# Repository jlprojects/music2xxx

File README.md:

# music2xxx
## Hybrid Music 2000 Clone Midi I/O PCB

This is a hardware clone of the Hybrid Music 2000 Midi add-on for the Acorn BBC Microcomputer model B and Master 128 designed for use with the Hybrid Music 5000 system. It is designed to stack on the Music5xxx clone PCB, and uses the 5V supply from the main board. If used independently of the Music5xxx, you will need to provide a 5V supply - this can come from the BBC Micro's auxiliary power connector.

The Music 2000 Midi interface combined with the AMPLE programming language and the Hybrid Studio 5000 Studio software provides versatile control of external Midi devices. The Music 2000 has 3 Midi output sockets.

Despite having an on-board Midi input port, AMPLE and the Hybrid System cannot use it directly. It is assumed that the Hybrid system is used as a controller and sequencer. However, it is possible to address the interface from user programs.

## The clone

It is designed in Kicad, based upon Colin Fraser's reverse-engineered schematic. http://www.colinfraser.com/m5000/m2000sch.pdf This version uses a different opto-isolator on the Midi input, and implements activity LEDs for the Midi outputs. 

Currently all the 74xx series logic ICs are available new. The 6850 UART ICs are no longer manufactured, but are commonly available second-hand or new-old-stock. 

4/9/19 For standalone use, an optional LM7805 regulator is added to allow powering the board from 9V-12V, as well as an LED to show input activity. A few prototype PCBs have been ordered.

## Using outside the Hybrid system

It's possible to use the m2000 Midi interface in BASIC or machine code - the 6850 Uarts can be read to or written to at addresses: 

* FC08/9 ACIA 1 (MIDI OUT 1)
* FC0A/B ACIA 2 (MIDI OUT 2)
* FC0C/D ACIA 3 (MIDI OUT 3, MIDI IN)

Info from: http://mdfs.net/Info/Comp/BBC/MIDI/m2000

## Resources

* Colin Fraser's Music5000 Resources: http://www.colinfraser.com/m5000/m5000.htm

* The Music2000 Interface User Guide covers all aspects of controlling Midi instruments with AMPLE and Studio 5000. It's available on the retro-kit archive page describing the Hybrid Music 2000: https://www.retro-kit.co.uk/page.cfm/content/Hybrid-Music-2000-Interface/

* A comprehensive archive about the Hybrid Music System: https://www.retro-kit.co.uk/page.cfm/content/Hybrid-Music-5000-Synthesiser/

* Here's the Stardot thread about this project: https://stardot.org.uk/forums/viewtopic.php?f=3&t=16895

* The Stardot 8bit hardware forum often has posts about the Hybrid Music system: https://stardot.org.uk/forums/viewforum.php?f=3

* Information about Midi on the BBC Microcomputer: http://mdfs.net/Info/Comp/BBC/MIDI/

## Licence

Unless otherwise marked, work in this repository is licenced under [Creative Commons Attribution-ShareAlike 4.0 International License](http://creativecommons.org/licenses/by-sa/4.0/)

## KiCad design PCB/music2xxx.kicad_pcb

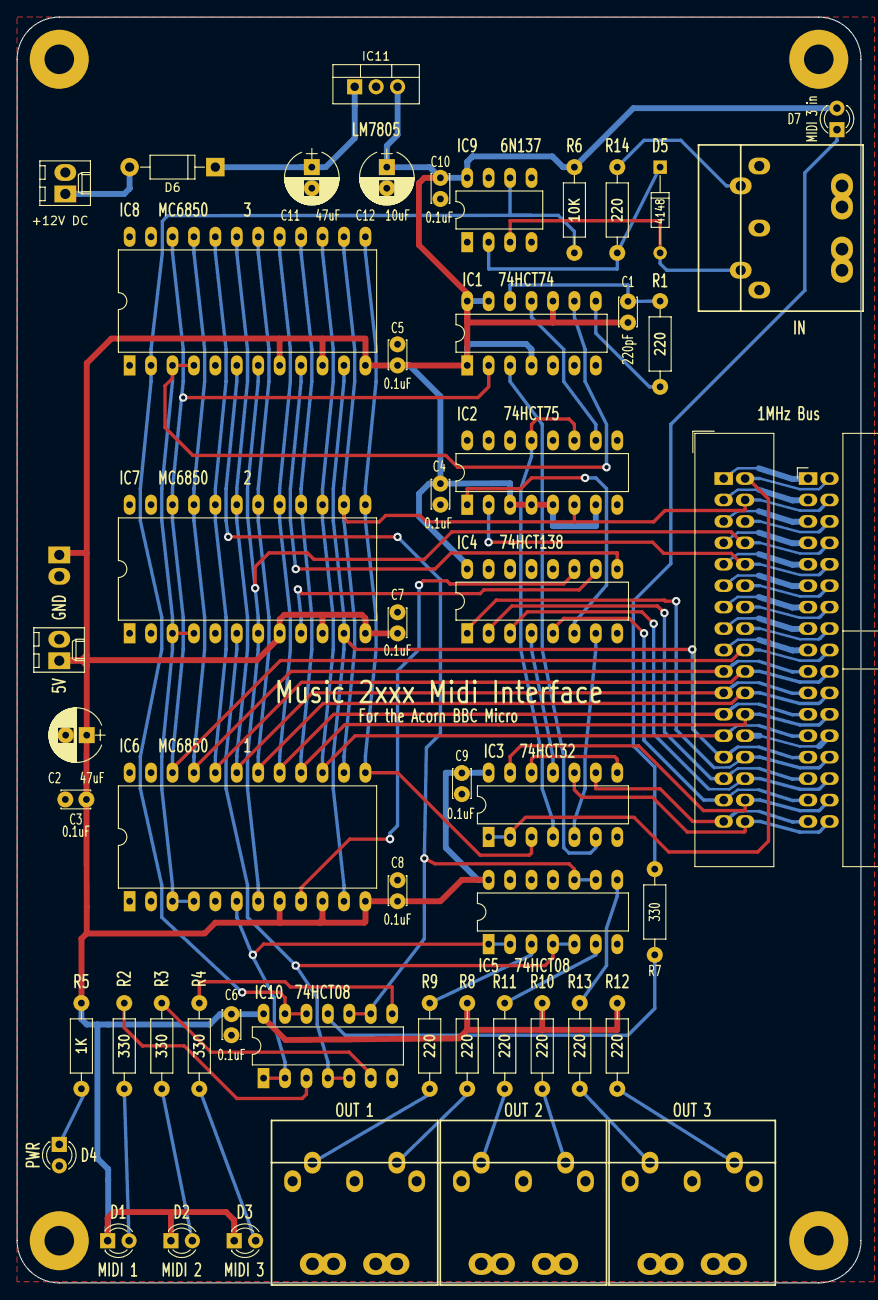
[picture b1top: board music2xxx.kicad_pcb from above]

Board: 2 copper layers, 100.0 x 150.0 mm, 57 parts (1 on the bottom side), 67 nets.

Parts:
C1: 220pF; C_Disc_D3.4mm_W2.1mm_P2.50mm
C2, C11: 47uF; CP_Radial_D6.3mm_P2.50mm
C3, C4, C5, C6, C7, C8, C9, C10: 0.1uF; C_Disc_D3.4mm_W2.1mm_P2.50mm
C12: 10uF; CP_Radial_D6.3mm_P2.50mm
D1: MIDI 1; LED_D3.0mm
D2: MIDI 2; LED_D3.0mm
D3: MIDI 3; LED_D3.0mm
D4: PWR; LED_D3.0mm
D5: 4148; D_DO-35_SOD27_P10.16mm_Horizontal
D6: 1N4001; D_DO-41_SOD81_P10.16mm_Horizontal
D7: MIDI 3 in; LED_D3.0mm
H1, H2, H3, H4: 3.5mm; MountingHole_3.5mm_Pad
IC1: 74HCT74; DIP-14_W7.62mm_LongPads
IC2: 74HCT75; DIP-16_W7.62mm_LongPads
IC3: 74HCT32; DIP-14_W7.62mm_LongPads
IC4: 74HCT138; DIP-16_W7.62mm_LongPads
IC5, IC10: 74HCT08; DIP-14_W7.62mm_LongPads
IC6, IC7, IC8: MC6850; DIP-24_W15.24mm_LongPads
IC9: 6N137; DIP-8_W7.62mm_LongPads
IC11: LM7805_TO220; TO-220-3_Vertical
J1: 1MHzBus1; IDC-Header_2x17_Pitch2.54mm_Angled
J2: 1MHzBus2; IDC-Header_2x17_Pitch2.54mm_Straight
J3, J4: +5V; Molex_KK-6410-02_02x2.54mm_Straight
J5: OUT 1; din_5_pcb_mount
J6: OUT 2; din_5_pcb_mount
J7: OUT 3; din_5_pcb_mount
J8: IN; din_5_pcb_mount
J9: +12V DC; Molex_KK-6410-02_02x2.54mm_Straight
R1, R8, R9, R10, R11, R12, R13, R14: 220; R_Axial_DIN0207_L6.3mm_D2.5mm_P10.16mm_Horizontal
R2, R3, R4, R7: 330; R_Axial_DIN0207_L6.3mm_D2.5mm_P10.16mm_Horizontal
R5: 1K; R_Axial_DIN0207_L6.3mm_D2.5mm_P10.16mm_Horizontal
R6: 10K; R_Axial_DIN0207_L6.3mm_D2.5mm_P10.16mm_Horizontal

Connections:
+5V: C1.1, C2.1, C3.1, C4.1, C5.1, C6.1, C7.1, C8.1, C9.1, C10.1, C12.1, D1.2, D2.2, D3.2, D7.2, IC1.1, IC1.4, IC1.10, IC1.13, IC1.14, IC2.3, IC2.4, IC2.5, IC2.7, IC3.14, IC4.16, IC5.14, IC6.8, IC6.10, IC6.12, IC7.8, IC7.10, IC7.12, IC8.8, IC8.10, IC8.12, IC9.8, IC10.14, IC11.3, J3.1, J4.1, R5.1, R6.2, R8.1, R10.1, R12.1
/1MHZE: IC2.6, IC6.14, IC7.14, IC8.14, J1.4, J2.4
/AUDIO: J1.16, J2.16
/R~W: IC3.1, IC3.2, J1.2, J2.2
/a0: IC6.11, IC7.11, IC8.11, J1.27, J2.27
/a1: IC4.1, J1.28, J2.28
/a2: IC4.2, J1.29, J2.29
/a3: IC4.3, J1.30, J2.30
/a4: IC4.5, J1.31, J2.31
/a5: IC3.13, J1.32, J2.32
/a6: IC3.9, J1.33, J2.33
/a7: IC3.10, J1.34, J2.34
/d0: IC1.2, IC6.22, IC7.22, IC8.22, J1.18, J2.18
/d1: IC6.21, IC7.21, IC8.21, J1.19, J2.19
/d2: IC6.20, IC7.20, IC8.20, J1.20, J2.20
/d3: IC6.19, IC7.19, IC8.19, J1.21, J2.21
/d4: IC6.18, IC7.18, IC8.18, J1.22, J2.22
/d5: IC6.17, IC7.17, IC8.17, J1.23, J2.23
/d6: IC6.16, IC7.16, IC8.16, J1.24, J2.24
/d7: IC6.15, IC7.15, IC8.15, J1.25, J2.25
/~IRQ: IC6.7, IC7.7, IC8.7, J1.8, J2.8
/~NMI: J1.6, J2.6
/~PGFC: IC2.2, J1.10, J2.10
/~PGFD: J1.12, J2.12
/~RST: J1.14, J2.14
CLK-6850: IC1.9, IC6.3, IC6.4, IC7.3, IC7.4, IC8.3, IC8.4
CP1-1: IC1.3, IC3.6
CP2-1: IC1.11, IC2.10
CS2-1: IC4.11, IC6.9
CS2-2: IC4.10, IC7.9
CS2-3: IC4.9, IC8.9
GND: C2.2, C3.2, C4.2, C5.2, C6.2, C7.2, C8.2, C9.2, C10.2, C11.2, C12.2, D4.1, IC1.7, IC2.12, IC3.7, IC4.8, IC5.7, IC5.12, IC5.13, IC6.1, IC6.2, IC6.23, IC6.24, IC7.1, IC7.2, IC7.23, IC7.24, IC8.1, IC8.23, IC8.24, IC9.5, IC10.7, IC11.2, J1.1, J1.3, J1.5, J1.7, J1.9, J1.11, J1.13, J1.15, J1.17, J1.26, J2.1, J2.3, J2.5, J2.7, J2.9, J2.11, J2.13, J2.15, J2.17, J2.26, J3.2, J4.2, J5.2, J6.2, J7.2, J9.2
unnamed: C1.2, IC1.12, R1.2
unnamed: C11.1, D6.1, IC11.1
unnamed: D1.1, R2.2
unnamed: D2.1, R3.2
unnamed: D3.1, R4.2
unnamed: D4.2, R5.2
unnamed: D5.1, IC9.2, R14.1
unnamed: D5.2, IC9.3, J8.5
unnamed: D6.2, J9.1
unnamed: D7.1, R7.2
unnamed: IC1.8, R1.1
unnamed: IC2.1, IC4.6
unnamed: IC2.11, IC2.13, IC3.4
unnamed: IC3.5, IC4.7
unnamed: IC3.11, IC4.4
unnamed: IC3.8, IC3.12
unnamed: IC5.3, R9.1
unnamed: IC5.6, R11.1
unnamed: IC5.8, R13.1
unnamed: IC10.3, R2.1
unnamed: IC10.6, R3.1
unnamed: IC10.8, R4.1
unnamed: IC10.11, R7.1
unnamed: J5.4, R8.2
unnamed: J5.5, R9.2
unnamed: J6.4, R10.2
unnamed: J6.5, R11.2
unnamed: J7.4, R12.2
unnamed: J7.5, R13.2
unnamed: J8.4, R14.2
RX3: IC8.2, IC9.6, IC10.12, IC10.13, R6.1
R~W~': IC3.3, IC6.13, IC7.13, IC8.13
TX1: IC5.1, IC5.2, IC6.6, IC10.1, IC10.2
TX2: IC5.4, IC5.5, IC7.6, IC10.4, IC10.5
TX3: IC5.9, IC5.10, IC8.6, IC10.9, IC10.10

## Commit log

2019-09-04 Add 7805 regulator
